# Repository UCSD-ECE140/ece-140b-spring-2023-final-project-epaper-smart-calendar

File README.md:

DEVELOPMENT SETUP:
Development is conducted using VS Code; the following extensions are required:
1. CPP Support (OPTIONAL: Syntax highlighting, misc. QoL CPP Extensions)
2. Arduino

Press control+shift+P and open the arduino library manager, then search for and install the following libraries:
1. WiFi
2. HTTPClient
3. ArduinoJson

TODO: ADD INSTRUCTIONS FOR BOARD UPLOAD

MISC. UNSORTED RESOURCES:
https://github.com/me-no-dev/arduino-esp32fs-plugin

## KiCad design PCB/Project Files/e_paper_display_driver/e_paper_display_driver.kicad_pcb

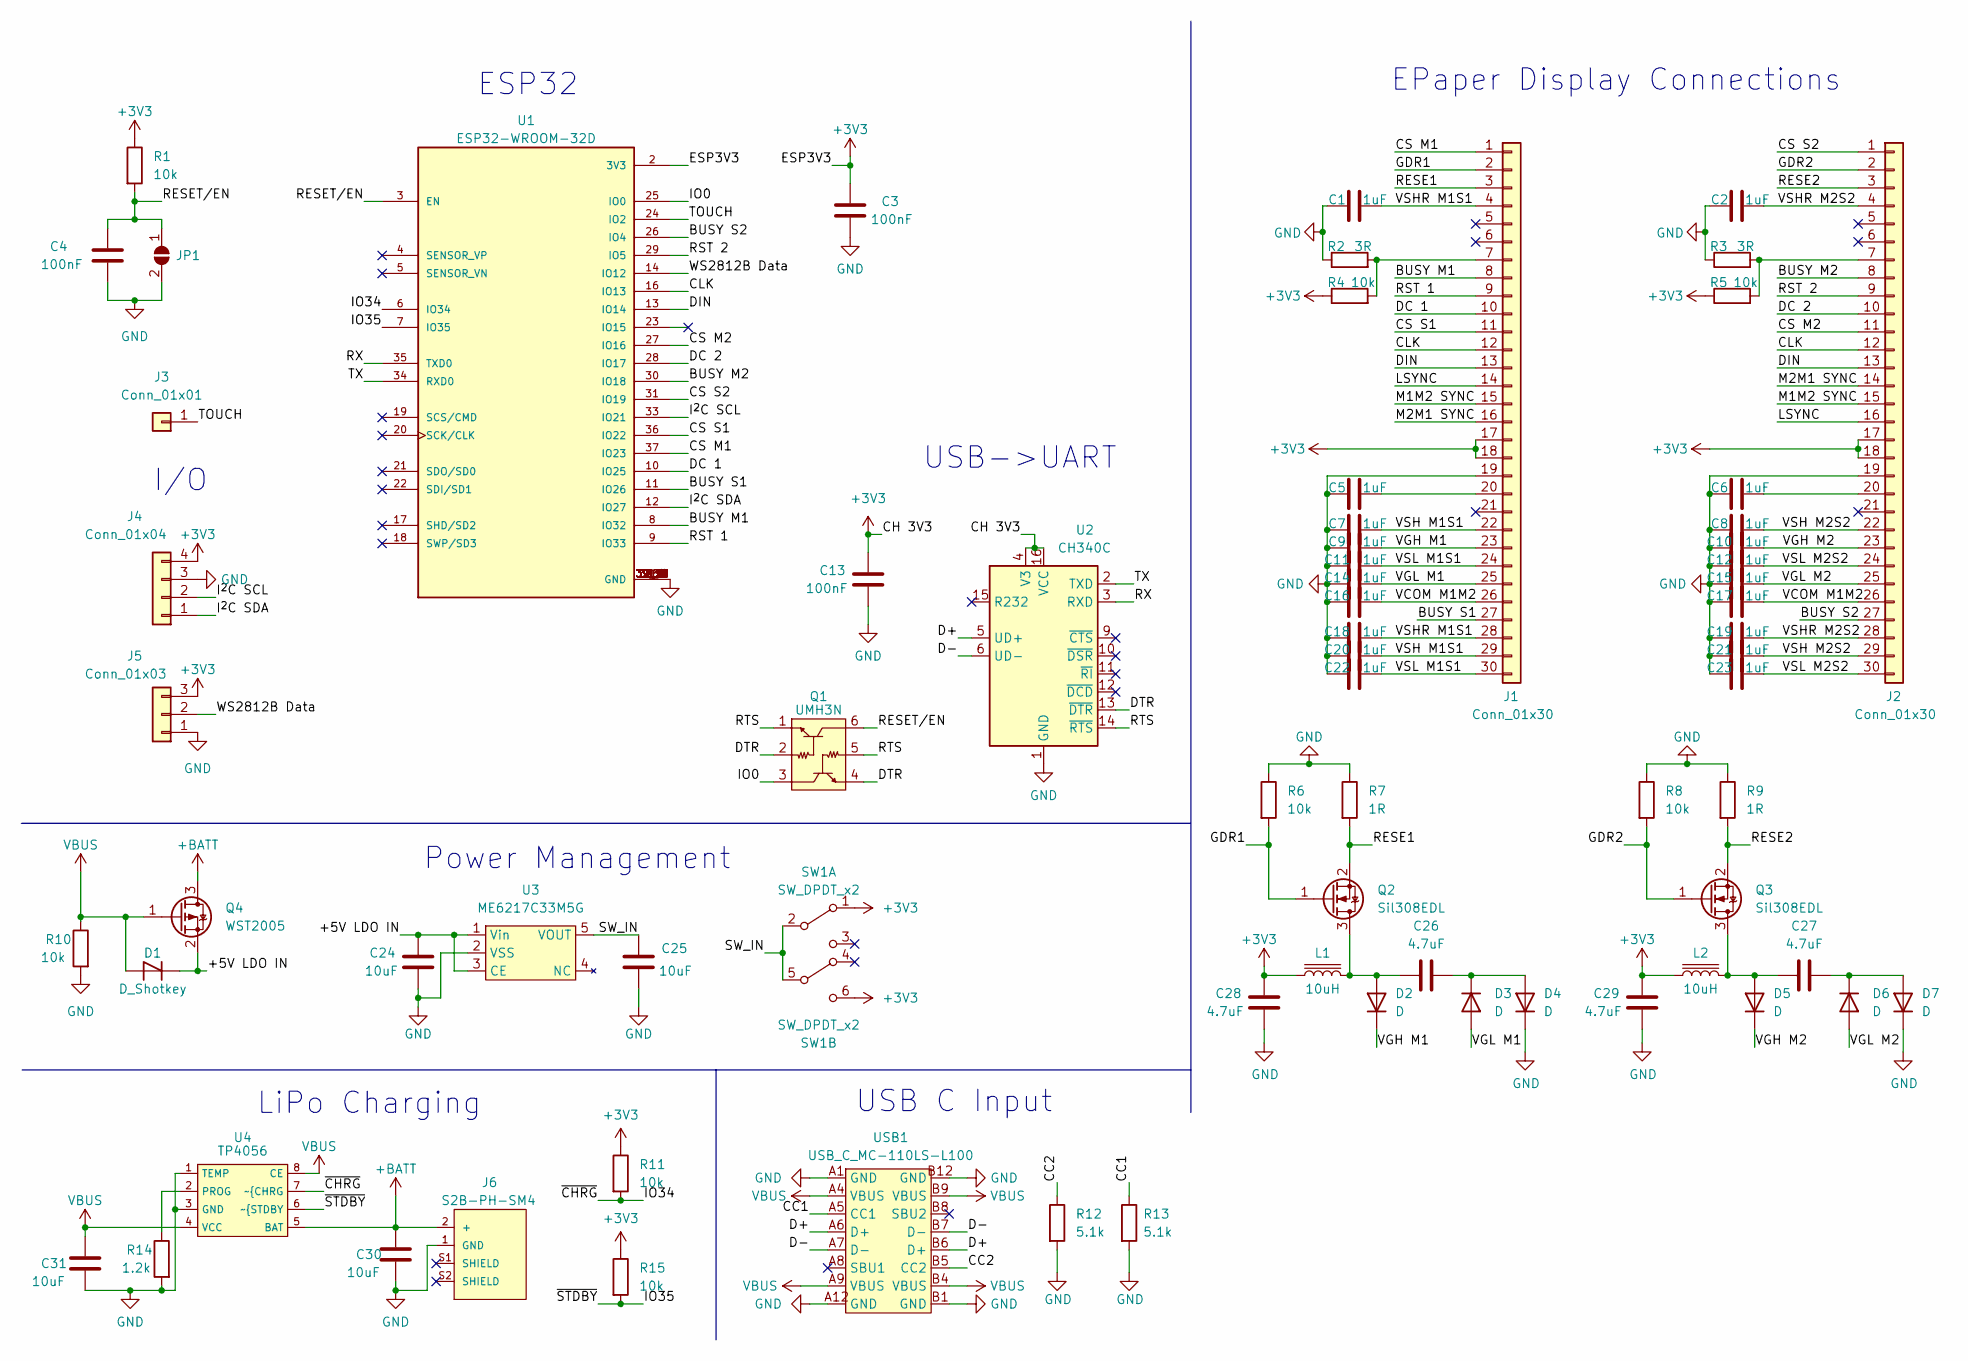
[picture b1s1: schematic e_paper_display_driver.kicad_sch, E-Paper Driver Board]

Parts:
C1, C2, C5, C6, C7, C8, C9, C10, C11, C12, C14, C15, C16, C17, C18, C19, C20, C21, C22, C23: 1uF; C_0603_1608Metric
C3, C4, C13: 100nF; C_0603_1608Metric
C24, C25, C30, C31: 10uF; C_0603_1608Metric
C26, C27, C28, C29: 4.7uF; C_0603_1608Metric
D1: D_Shotkey; D_SOD-123
D2, D3, D4, D5, D6, D7: D; D_SOD-123
J1, J2: Conn_01x30; Hirose_FH12-30S-0.5SH_1x30-1MP_P0.50mm_Horizontal
J3: Conn_01x01
J4: Conn_01x04; PinHeader_1x04_P2.54mm_Vertical
J5: Conn_01x03; PinHeader_1x03_P2.54mm_Vertical
J6: S2B-PH-SM4; JST_S2B-PH-SM4-TB(LF)(SN)
JP1: SolderJumper_2_Open; SolderJumper-2_P1.3mm_Open_Pad1.0x1.5mm
L1, L2: 10uH; L_WPN4020H100MT
Q1: UMH3N; SOT-363_SC-70-6
Q2, Q3: Sil308EDL; SOT-323_SC-70
Q4: WST2005; SOT-323_SC-70
R1, R4, R5, R6, R8, R10, R11, R15: 10k; R_0603_1608Metric
R2, R3: 3R; R_0603_1608Metric
R7, R9: 1R; R_0603_1608Metric
R12, R13: 5.1k; R_0603_1608Metric
R14: 1.2k; R_0603_1608Metric
SW1: SW_DPDT_x2; TK-6580S-1
U1: ESP32-WROOM-32D; MODULE_ESP32-WROOM-32D; PARTREV 1.9
U2: CH340C; SOIC-16_3.9x9.9mm_P1.27mm
U3: ME6217C33M5G; SOT-23-5
U4: TP4056; HTSOP-8-1EP_3.9x4.9mm_P1.27mm_EP2.4x3.2mm
USB1: USB_C_MC-110LS-L100; MC-110LS-L100

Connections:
+3V3: C3.1, C13.1, C28.1, C29.1, J1.17, J1.18, J2.17, J2.18, J4.4, J5.3, L1.1, L2.1, R1.1, R4.1, R5.1, R11.1, R15.1, SW1.1 (A), SW1.6 (C), U1.2 (3V3), U2.4 (V3), U2.16 (VCC)
+BATT: C30.1, J6.2 (+), Q4.3 (D), U4.5 (BAT)
/+5V LDO IN: C24.1, D1.1 (K), Q4.2 (S), U3.1 (Vin), U3.3 (CE)
/BUSY M1: J1.8, U1.8 (IO32)
/BUSY M2: J2.8, U1.30 (IO18)
/BUSY S1: J1.27, U1.11 (IO26)
/BUSY S2: J2.27, U1.26 (IO4)
/CC1: R13.1, USB1.A5 (CC1)
/CC2: R12.1, USB1.B5 (CC2)
/CLK: J1.12, J2.12, U1.16 (IO13)
/CS M1: J1.1, U1.37 (IO23)
/CS M2: J2.11, U1.27 (IO16)
/CS S1: J1.11, U1.36 (IO22)
/CS S2: J2.1, U1.31 (IO19)
/D+: U2.5 (UD+), USB1.A6 (D+), USB1.B6 (D+)
/D-: U2.6 (UD-), USB1.A7 (D-), USB1.B7 (D-)
/DC 1: J1.10, U1.10 (IO25)
/DC 2: J2.10, U1.28 (IO17)
/DIN: J1.13, J2.13, U1.13 (IO14)
/DTR: Q1.2, Q1.4, U2.13 (~DTR)
/GDR1: J1.2, Q2.1 (G), R6.2
/GDR2: J2.2, Q3.1 (G), R8.2
/IO0: Q1.3, U1.25 (IO0)
/IO34: R11.2, U1.6 (IO34), U4.7 (~{CHRG)
/IO35: R15.2, U1.7 (IO35), U4.6 (~{STDBY)
/I^{2}C SCL: J4.2, U1.33 (IO21)
/I^{2}C SDA: J4.1, U1.12 (IO27)
/LSYNC: J1.14, J2.16
/M1M2 SYNC: J1.15, J2.15
/M2M1 SYNC: J1.16, J2.14
/RESE1: J1.3, Q2.2 (S), R7.2
/RESE2: J2.3, Q3.2 (S), R9.2
/RESET/EN: C4.1, JP1.1 (A), Q1.6, R1.2, U1.3 (EN)
/RST 1: J1.9, U1.9 (IO33)
/RST 2: J2.9, U1.29 (IO5)
/RTS: Q1.1, Q1.5, U2.14 (~RTS)
/RX: U1.35 (TXD0), U2.3 (RXD)
/SW_IN: C25.1, SW1.2 (B), SW1.5 (B), U3.5 (VOUT)
/TOUCH: J3.1, U1.24 (IO2)
/TX: U1.34 (RXD0), U2.2 (TXD)
/VCOM M1M2: C16.2, C17.2, J1.26, J2.26
/VGH M1: C9.2, D2.1 (K), J1.23
/VGH M2: C10.2, D5.1 (K), J2.23
/VGL M1: C14.2, D3.2 (A), J1.25
/VGL M2: C15.2, D6.2 (A), J2.25
/VSH M1S1: C7.2, C20.2, J1.22, J1.29
/VSH M2S2: C8.2, C21.2, J2.22, J2.29
/VSHR M1S1: C1.2, C18.2, J1.4, J1.28
/VSHR M2S2: C2.2, C19.2, J2.4, J2.28
/VSL M1S1: C11.2, C22.2, J1.24, J1.30
/VSL M2S2: C12.2, C23.2, J2.24, J2.30
/WS2812B Data: J5.2, U1.14 (IO12)
GND: C1.1, C2.1, C3.2, C4.2, C5.1, C6.1, C7.1, C8.1, C9.1, C10.1, C11.1, C12.1, C13.2, C14.1, C15.1, C16.1, C17.1, C18.1, C19.1, C20.1, C21.1, C22.1, C23.1, C24.2, C25.2, C28.2, C29.2, C30.2, C31.2, D4.1 (K), D7.1 (K), J1.19, J2.19, J4.3, J5.1, J6.1 (GND), JP1.2 (B), R2.1, R3.1, R6.1, R7.1, R8.1, R9.1, R10.2, R12.2, R13.2, R14.2, U1.1 (GND), U1.15 (GND), U1.38 (GND), U1.39_1 (GND), U1.39_2 (GND), U1.39_3 (GND), U1.39_4 (GND), U1.39_5 (GND), U1.39_6 (GND), U1.39_7 (GND), U1.39_8 (GND), U1.39_9 (GND), U1.39_10 (GND), U1.39_11 (GND), U1.39_12 (GND), U1.39_13 (GND), U1.39_14 (GND), U1.39_15 (GND), U1.39_16 (GND), U1.39_17 (GND), U1.39_18 (GND), U1.39_19 (GND), U1.39_20 (GND), U1.39_21 (GND), U2.1 (GND), U3.2 (VSS), U4.1 (TEMP), U4.3 (GND), USB1.A1 (GND), USB1.A12 (GND), USB1.B1 (GND), USB1.B12 (GND)
unnamed: C5.2, J1.20
unnamed: C6.2, J2.20
unnamed: C26.1, D2.2 (A), L1.2, Q2.3 (D)
unnamed: C26.2, D3.1 (K), D4.2 (A)
unnamed: C27.1, D5.2 (A), L2.2, Q3.3 (D)
unnamed: C27.2, D6.1 (K), D7.2 (A)
unnamed: J1.7, R2.2, R4.2
unnamed: J2.7, R3.2, R5.2
unnamed: R14.1, U4.2 (PROG)
VBUS: C31.1, D1.2 (A), Q4.1 (G), R10.1, U4.4 (VCC), U4.8 (CE), USB1.A4 (VBUS), USB1.A9 (VBUS), USB1.B4 (VBUS), USB1.B9 (VBUS)

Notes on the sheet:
I/O
EPaper Display Connections
USB->UART
USB C Input
LiPo Charging
Power Management
ESP32

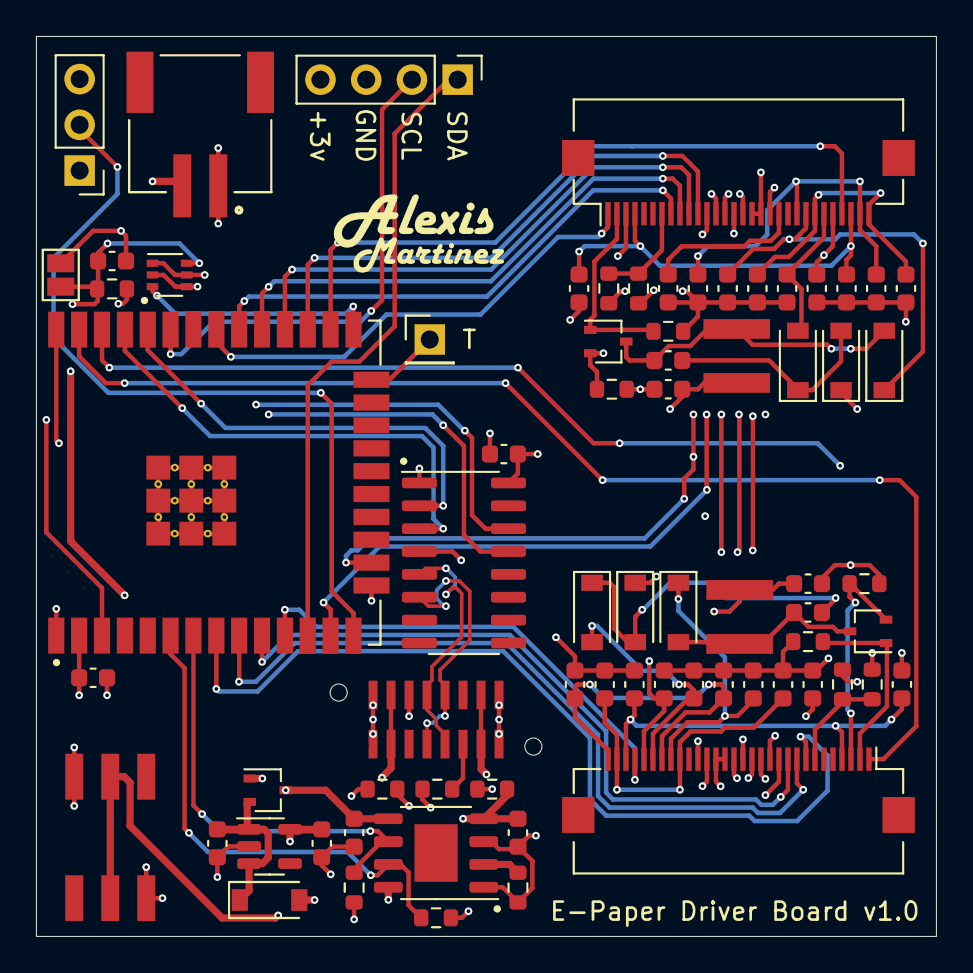
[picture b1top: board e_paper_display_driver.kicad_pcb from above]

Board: 4 copper layers, 50.0 x 50.0 mm, 72 parts (0 on the bottom side), 63 nets.

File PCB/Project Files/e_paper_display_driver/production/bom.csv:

Designator,Footprint,Quantity,Value,LCSC Part #
"C1, C10, C11, C12, C14, C15, C16, C17, C18, C19, C2, C20, C21, C22, C23, C5, C6, C7, C8, C9",0603,20,1uF,
"C13, C3, C4",0603,3,100nF,
"C24, C25, C30, C31",0603,4,10uF,
"C26, C27, C28, C29",0603,4,4.7uF,
D1,D_SOD-123,1,D_Shotkey,
"D2, D3, D4, D5, D6, D7",D_SOD-123,6,D,
"J1, J2",Hirose_FH12-30S-0.5SH_1x30-1MP_P0.50mm_Horizontal,2,Conn_01x30,
J3,PinHeader_1x01_P2.54mm_Vertical,1,Conn_01x01,
J4,PinHeader_1x04_P2.54mm_Vertical,1,Conn_01x04,
J5,PinHeader_1x03_P2.54mm_Vertical,1,Conn_01x03,
J6,JST_S2B-PH-SM4-TB(LF)(SN),1,S2B-PH-SM4,
JP1,SolderJumper-2_P1.3mm_Open_Pad1.0x1.5mm,1,SolderJumper_2_Open,
"L1, L2",L_WPN4020H100MT,2,10uH,
Q1,SOT-363_SC-70-6,1,UMH3N,
"Q2, Q3",SOT-323_SC-70,2,Sil308EDL,
Q4,SOT-323_SC-70,1,WST2005,
"R1, R10, R11, R15, R4, R5, R6, R8",0603,8,10k,
"R12, R13",0603,2,5.1k,
R14,0603,1,1.2k,
"R2, R3",0603,2,3R,
"R7, R9",0603,2,1R,
SW1,TK-6580S-1,1,SW_DPDT_x2,
U1,MODULE_ESP32-WROOM-32D,1,ESP32-WROOM-32D,
U2,SOIC-16_3.9x9.9mm_P1.27mm,1,CH340C,
U3,SOT-23-5,1,ME6217C33M5G,
U4,HTSOP-8-1EP_3.9x4.9mm_P1.27mm_EP2.4x3.2mm,1,TP4056,
USB1,MC-110LS-L100,1,USB_C_MC-110LS-L100,

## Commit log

2023-04-27 Added PCB Stuff
2023-04-27 Added Initial CAD Files and Display Measurements
2023-04-28 Deleted Old CAD Files
2023-04-28 Updated CAD Files
2023-05-02 PDF Schematic
2023-05-17 PCB Updates
2023-05-17 Stashed old firmware and updated with working codebase.
